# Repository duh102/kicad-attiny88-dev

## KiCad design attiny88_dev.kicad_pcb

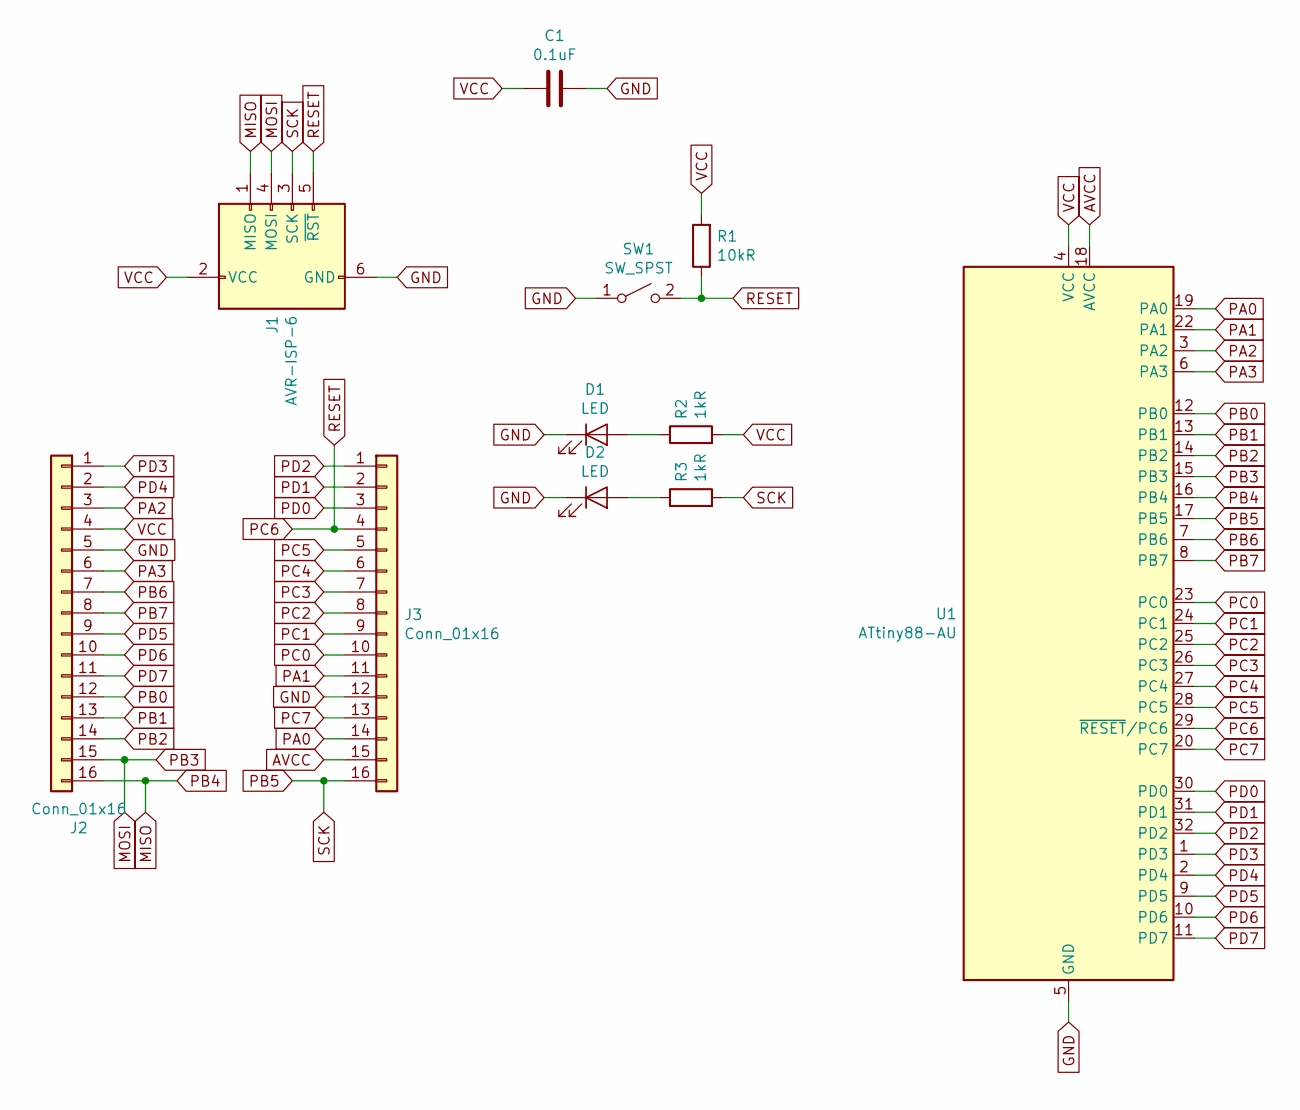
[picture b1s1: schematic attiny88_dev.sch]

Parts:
C1: 0.1uF; C_0805_2012Metric
D1, D2: LED; LED_0805_2012Metric
J1: AVR-ISP-6; PinHeader_2x03_P2.54mm_Vertical
J2, J3: Conn_01x16; PinHeader_1x16_P2.54mm_Vertical
R1: 10kR; R_0805_2012Metric
R2, R3: 1kR; R_0805_2012Metric
SW1: SW_SPST; SW_SPST_GENERIC_6x3.7mm_2_PAD
U1: ATtiny88-AU; TQFP-32_7x7mm_P0.8mm

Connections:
AVCC: J3.15, U1.18 (AVCC)
GND: C1.2, D1.1 (K), D2.1 (K), J1.6 (GND), J2.5, J3.12, SW1.1 (A), U1.5 (GND), U1.21 (GND); also elsewhere on the board
MISO: J1.1 (MISO), J2.16, U1.16 (PB4)
MOSI: J1.4 (MOSI), J2.15, U1.15 (PB3)
unnamed: D1.2 (A), R2.1
unnamed: D2.2 (A), R3.1
PA0: J3.14, U1.19 (PA0)
PA1: J3.11, U1.22 (PA1)
PA2: J2.3, U1.3 (PA2)
PA3: J2.6, U1.6 (PA3)
PB0: J2.12, U1.12 (PB0)
PB1: J2.13, U1.13 (PB1)
PB2: J2.14, U1.14 (PB2)
PB5: J1.3 (SCK), J3.16, R3.2, U1.17 (PB5)
PB6: J2.7, U1.7 (PB6)
PB7: J2.8, U1.8 (PB7)
PC0: J3.10, U1.23 (PC0)
PC1: J3.9, U1.24 (PC1)
PC2: J3.8, U1.25 (PC2)
PC3: J3.7, U1.26 (PC3)
PC4: J3.6, U1.27 (PC4)
PC5: J3.5, U1.28 (PC5)
PC6: J1.5 (~RST), J3.4, R1.1, SW1.2 (B), U1.29 (~RESET~/PC6); also elsewhere on the board
PC7: J3.13, U1.20 (PC7)
PD0: J3.3, U1.30 (PD0)
PD1: J3.2, U1.31 (PD1)
PD2: J3.1, U1.32 (PD2)
PD3: J2.1, U1.1 (PD3)
PD4: J2.2, U1.2 (PD4)
PD5: J2.9, U1.9 (PD5)
PD6: J2.10, U1.10 (PD6)
PD7: J2.11, U1.11 (PD7)
VCC: C1.1, J1.2 (VCC), J2.4, R1.2, R2.2, U1.4 (VCC)

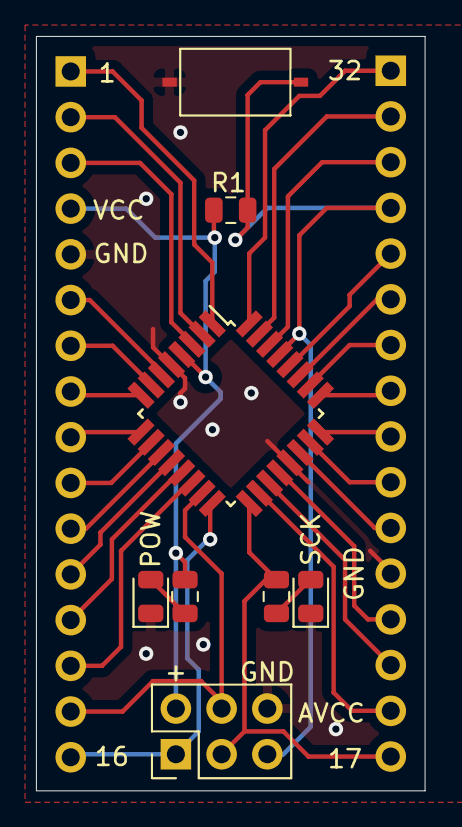
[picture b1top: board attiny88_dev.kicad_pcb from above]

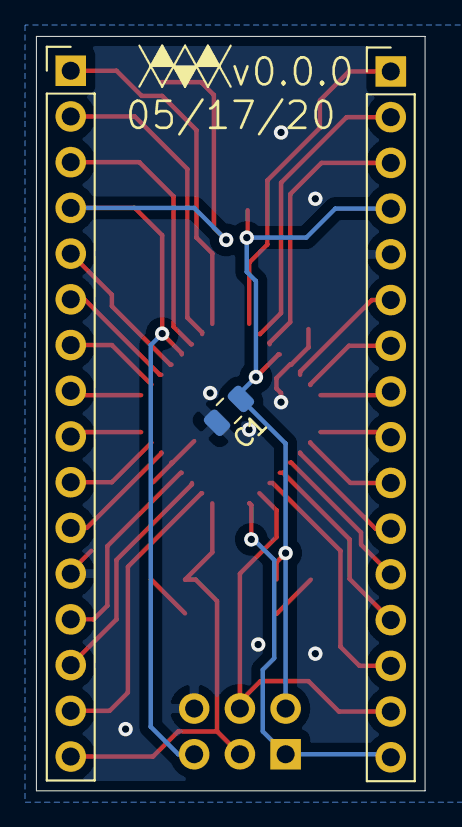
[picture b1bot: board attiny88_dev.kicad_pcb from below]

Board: 2 copper layers, 21.6 x 41.9 mm, 11 parts (3 on the bottom side), 33 nets.

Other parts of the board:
RESET: SW_SPST; SW_SPST_GENERIC_6x3.7mm_2_PAD

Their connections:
GND: RESET.1; also elsewhere on the board
PC6: RESET.2; also elsewhere on the board

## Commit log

2020-05-17 Add outputs
